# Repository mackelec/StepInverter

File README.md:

# StepInverter
These are the Files and Tools for my Step Inverter based on Tony's (WarpSpeed) designs and ideas.
You'll find me, "MackOffGrid" and Tony, "WarpSpeed" on https://www.thebackshed.com/forum/forum_topics.asp?FID=4 

Please keep in mind that the spreadsheet, software and schematics are not polished for public consumption, I created them for myself to get the job done.

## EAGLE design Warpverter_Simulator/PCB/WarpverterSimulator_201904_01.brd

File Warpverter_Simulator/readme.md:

# Warpverter Simulator

The simulator reads the signals from a Warpverter of any kind, and produces an analog output that you can view using a Scope.  It can also capture a frame of data and send the data to a PC.

## Instruction

This PCB plugs into the 38 pin header of tha Aduno DUE.

Then plug the outputs of Tony's Inverter, or stm32_Warpverter, into the matching connectors of the simulator PCB.
Connect your oscilloscope to DAC0 of the DUE to see the synthesized waveform.

Press the button on the simulator PCB and it will grab a frame of data and send it (by USB) to your PC.  Using the Arduino IDE serial monitor is the easiest way.

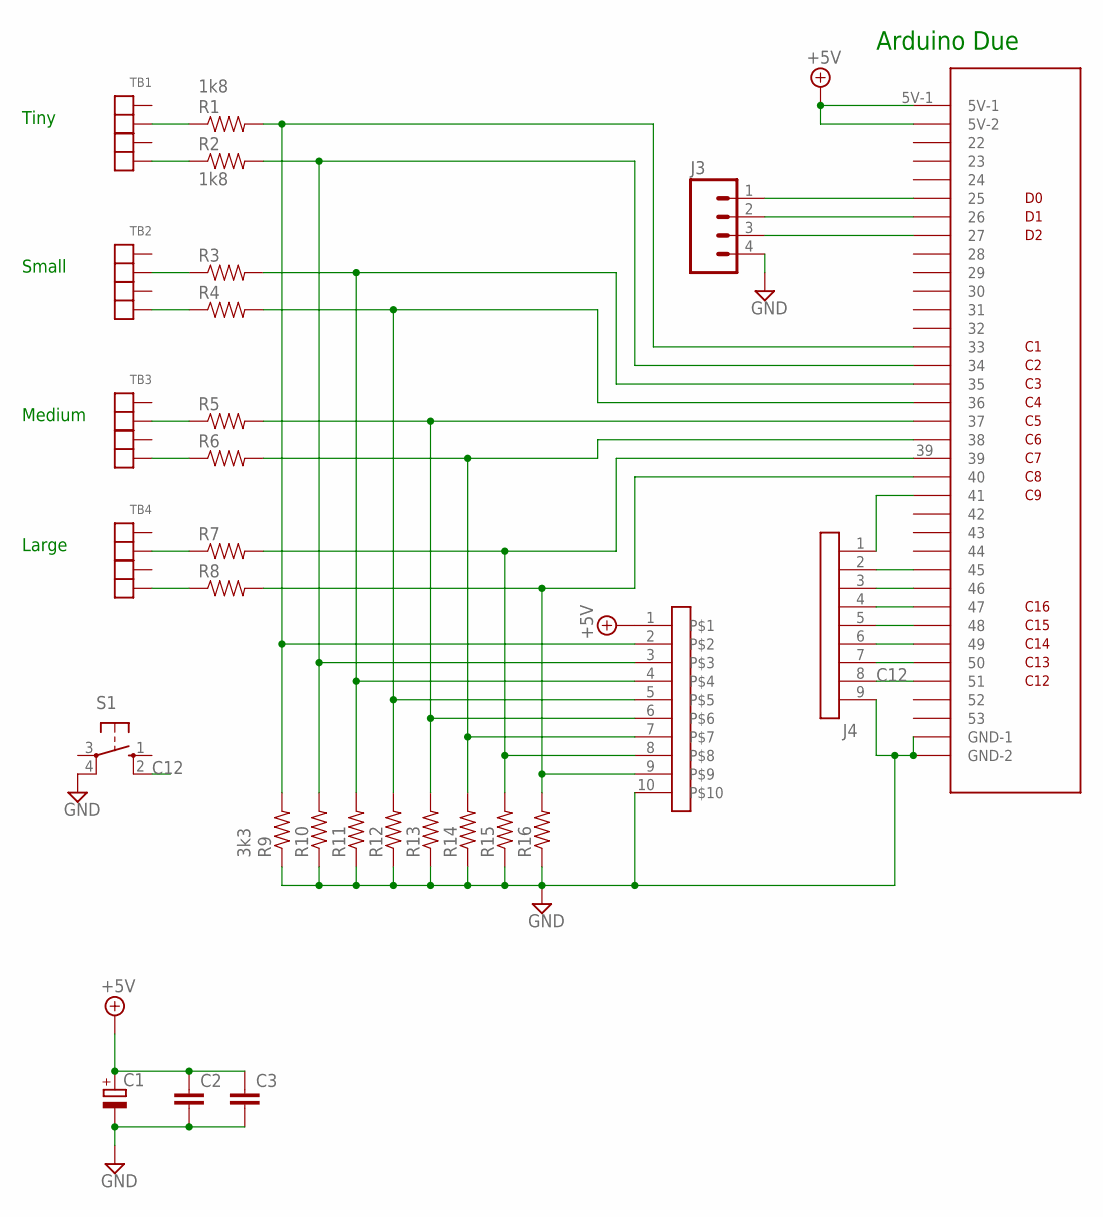
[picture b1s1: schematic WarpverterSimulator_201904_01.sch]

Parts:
C1: C-RB200100; CPOL-RADIAL-10UF-25V
C2, C3: BCAP
J1: DUE-IDC38
J2: SIL-STACK-10
J3: SIL4
J4: SIL-9
R1, R2: 1k8; AXIAL-0.4
R3, R4, R5, R6, R7, R8, R10, R11, R12, R13, R14, R15, R16: R4; AXIAL-0.4
R9: 3k3; AXIAL-0.4
S1: 10-XX; B3F-10XX
TB1, TB2, TB3, TB4: TB4381_SIL; TB-381-SIL-4P

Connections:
+5V: C1.1 (+), C2.1, C3.1, J1.5V-1, J1.5V-2, J2.1
C12: J1.51, J4.8, S1.2 (S1)
GND: C1.2 (-), C2.2, C3.2, J1.GND-1, J1.GND-2, J2.10, J3.4, J4.9, R9.P$1 (1), R10.P$1 (1), R11.P$1 (1), R12.P$1 (1), R13.P$1 (1), R14.P$1 (1), R15.P$1 (1), R16.P$1 (1), S1.4 (P1)
unnamed: R1.P$1 (1), TB1.2, TB1.12 (2)
unnamed: R2.P$1 (1), TB1.4, TB1.14 (4)
unnamed: R3.P$1 (1), TB2.2, TB2.12 (2)
unnamed: R4.P$1 (1), TB2.4, TB2.14 (4)
unnamed: R5.P$1 (1), TB3.2, TB3.12 (2)
unnamed: R6.P$1 (1), TB3.4, TB3.14 (4)
unnamed: R7.P$1 (1), TB4.2, TB4.12 (2)
unnamed: R8.P$1 (1), TB4.4, TB4.14 (4)
unnamed: J1.33, J2.2, R1.P$2 (2), R9.P$2 (2)
unnamed: J1.34, J2.3, R2.P$2 (2), R10.P$2 (2)
unnamed: J1.35, J2.4, R3.P$2 (2), R11.P$2 (2)
unnamed: J1.36, J2.5, R4.P$2 (2), R12.P$2 (2)
unnamed: J1.37, J2.6, R5.P$2 (2), R13.P$2 (2)
unnamed: J1.38, J2.7, R6.P$2 (2), R14.P$2 (2)
unnamed: J1.39, J2.8, R7.P$2 (2), R15.P$2 (2)
unnamed: J1.40, J2.9, R8.P$2 (2), R16.P$2 (2)
unnamed: J1.25, J3.1
unnamed: J1.26, J3.2
unnamed: J1.27, J3.3
unnamed: J1.50, J4.7
unnamed: J1.49, J4.6
unnamed: J1.48, J4.5
unnamed: J1.47, J4.4
unnamed: J1.46, J4.3
unnamed: J1.45, J4.2
unnamed: J1.41, J4.1

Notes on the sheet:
Tiny
Small
Medium
Large
Arduino Due

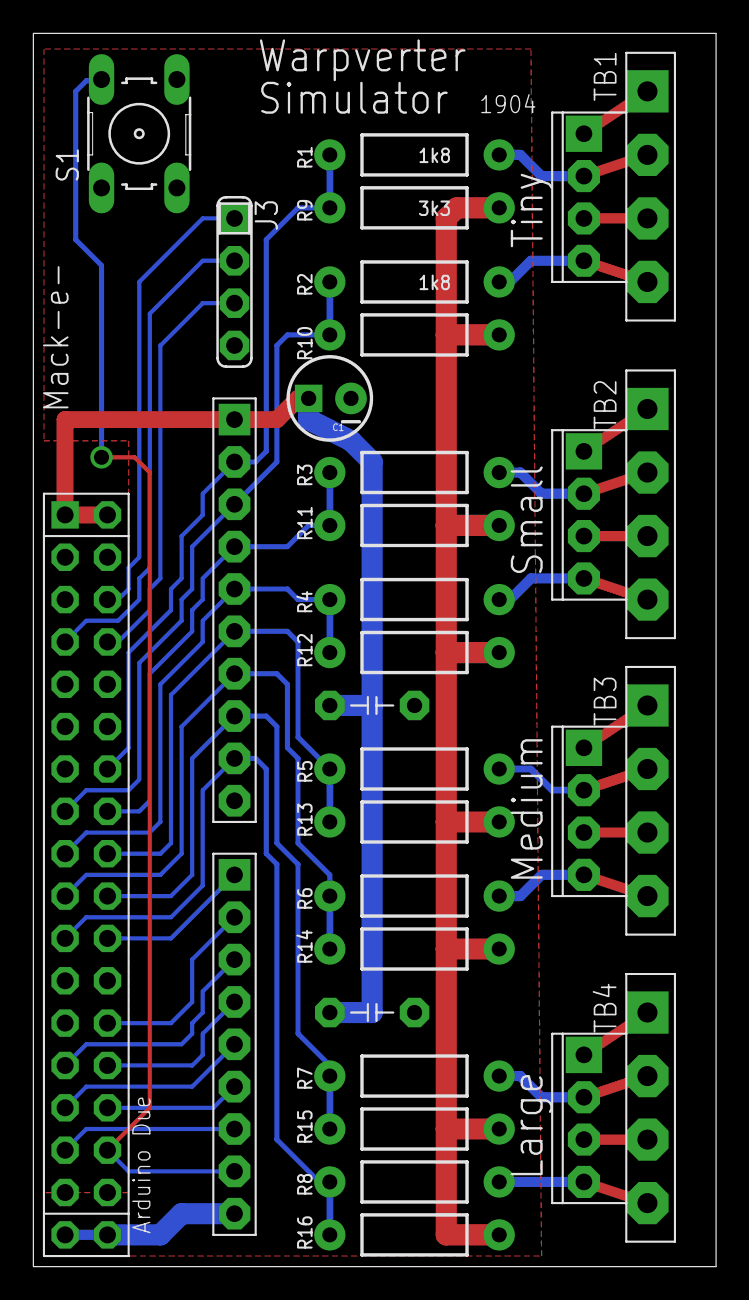
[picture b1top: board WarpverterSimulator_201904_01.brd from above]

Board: 2 copper layers, 40.9 x 74.0 mm, 28 parts (0 on the bottom side), 29 nets.

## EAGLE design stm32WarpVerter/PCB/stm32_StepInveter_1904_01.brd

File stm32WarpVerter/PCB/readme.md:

Zip Files contain EAGLE files and Gerber files.

For gerber viewer,  http://gerbv.geda-project.org/

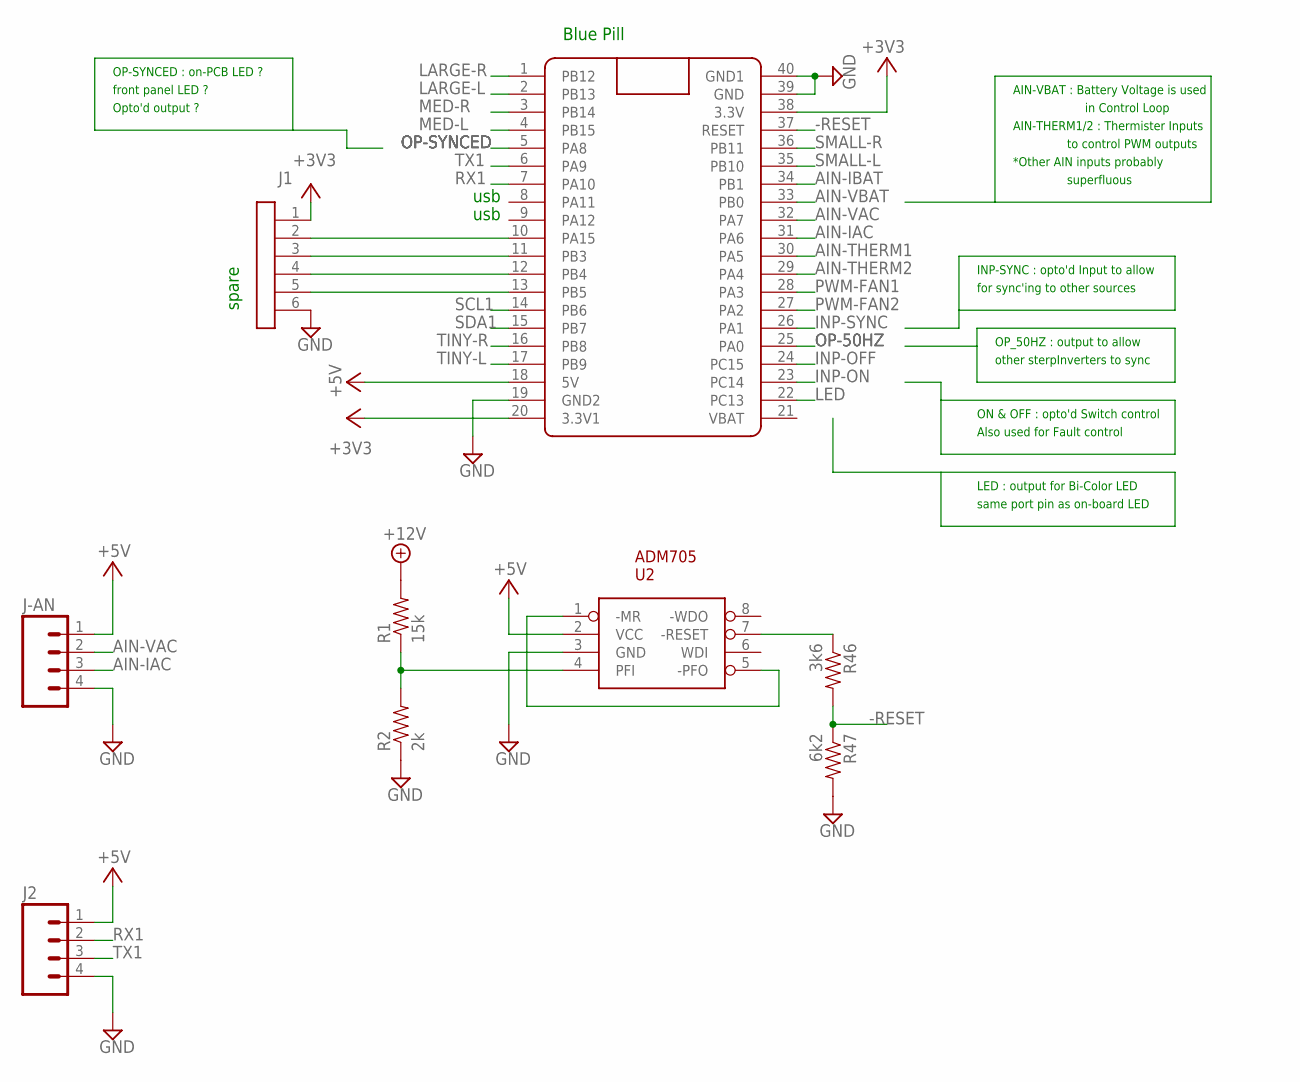
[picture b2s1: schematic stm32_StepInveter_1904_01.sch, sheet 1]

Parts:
J1: SIL-6; SIL6
J2: SIL4
J-AN: SIL4
R1: 15k; AXIAL-0.4
R2: 2k; AXIAL-0.4
R46: 3k6; AXIAL-0.4
R47: 6k2; AXIAL-0.4
U2: ADM705; DIL08
U$1: BLUE_PILL; BLUE_PILL_CLEAN

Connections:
+3V3: J1.1, U$1.20 (3.3V1), U$1.38 (3.3V); also elsewhere on the board
+5V: J2.1, J-AN.1, U2.2 (VCC), U$1.18 (5V); also elsewhere on the board
+12V: R1.P$2 (2); also elsewhere on the board
-RESET: R46.P$2 (2), R47.P$1 (1), U$1.37 (RESET)
AIN-IAC: J-AN.3, U$1.31 (PA6)
AIN-IBAT: U$1.34 (PB1); also elsewhere on the board
AIN-THERM1: U$1.30 (PA5); also elsewhere on the board
AIN-THERM2: U$1.29 (PA4); also elsewhere on the board
AIN-VAC: J-AN.2, U$1.32 (PA7)
AIN-VBAT: U$1.33 (PB0); also elsewhere on the board
GND: J1.6, J2.4, J-AN.4, R2.P$1 (1), R47.P$2 (2), U2.3 (GND), U$1.19 (GND2), U$1.39 (GND), U$1.40 (GND1); also elsewhere on the board
INP-OFF: U$1.24 (PC15); also elsewhere on the board
INP-ON: U$1.23 (PC14); also elsewhere on the board
INP-SYNC: U$1.26 (PA1); also elsewhere on the board
LARGE-L: U$1.2 (PB13); also elsewhere on the board
LARGE-R: U$1.1 (PB12); also elsewhere on the board
LED: U$1.22 (PC13); also elsewhere on the board
MED-L: U$1.4 (PB15); also elsewhere on the board
MED-R: U$1.3 (PB14); also elsewhere on the board
unnamed: J1.2, U$1.10 (PA15)
unnamed: J1.3, U$1.11 (PB3)
unnamed: J1.4, U$1.12 (PB4)
unnamed: J1.5, U$1.13 (PB5)
unnamed: U2.1 (-MR), U2.5 (-PFO)
unnamed: R1.P$1 (1), R2.P$2 (2), U2.4 (PFI)
unnamed: R46.P$1 (1), U2.7 (-RESET)
OP-50HZ: U$1.25 (PA0); also elsewhere on the board
OP-SYNCED: U$1.5 (PA8); also elsewhere on the board
PWM-FAN1: U$1.28 (PA3); also elsewhere on the board
PWM-FAN2: U$1.27 (PA2); also elsewhere on the board
RX1: J2.2, U$1.7 (PA10)
SCL1: U$1.14 (PB6)
SDA1: U$1.15 (PB7)
SMALL-L: U$1.35 (PB10); also elsewhere on the board
SMALL-R: U$1.36 (PB11); also elsewhere on the board
TINY-L: U$1.17 (PB9); also elsewhere on the board
TINY-R: U$1.16 (PB8); also elsewhere on the board
TX1: J2.3, U$1.6 (PA9)

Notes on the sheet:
usb
spare
Blue Pill
OP_50HZ : output to allow
other sterpInverters to sync
ON & OFF : opto'd Switch control
Also used for Fault control
LED : output for Bi-Color LED
same port pin as on-board LED
INP-SYNC : opto'd Input to allow
for sync'ing to other sources
OP-SYNCED : on-PCB LED ?
front panel LED ?
Opto'd output ?
AIN-VBAT : Battery Voltage is used
in Control Loop
AIN-THERM1/2 : Thermister Inputs
to control PWM outputs
*Other AIN inputs probably
superfluous

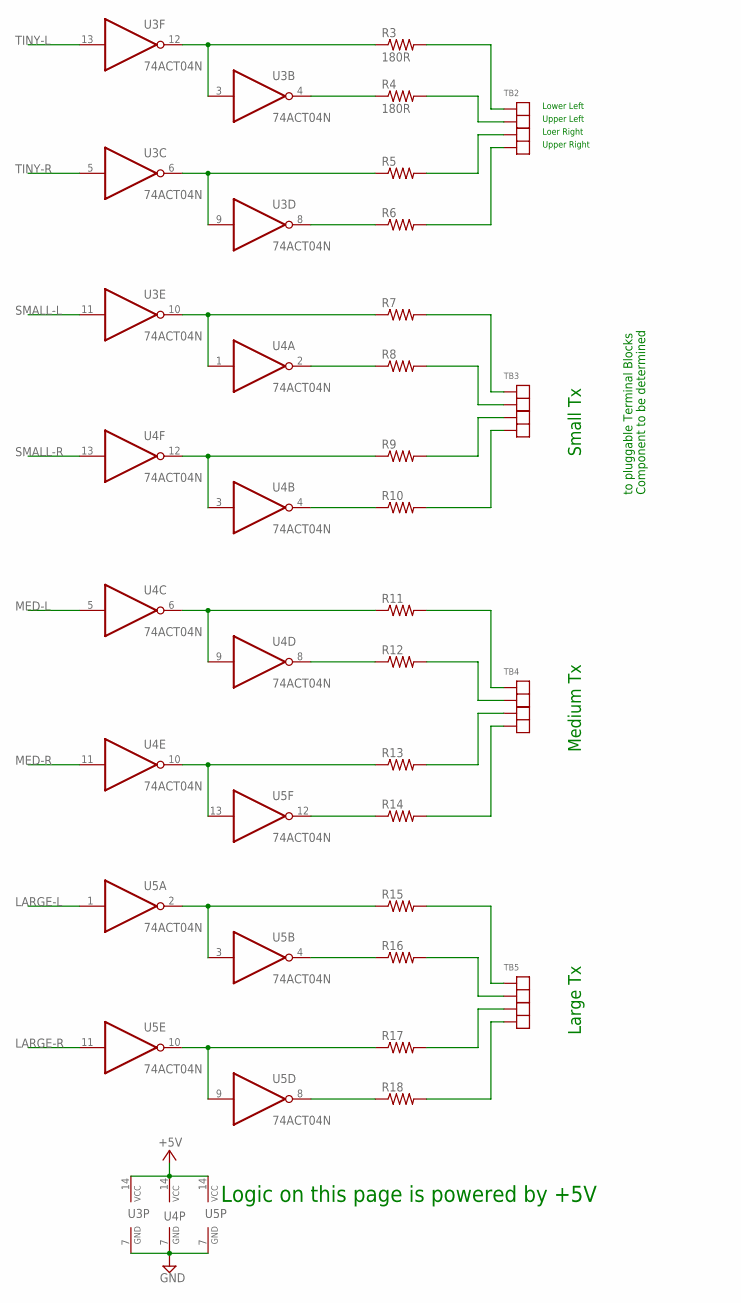
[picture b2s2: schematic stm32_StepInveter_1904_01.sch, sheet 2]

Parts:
R3, R4: 180R; AXIAL-0.4
R5, R6, R7, R8, R9, R10, R11, R12, R13, R14, R15, R16, R17, R18: R4; AXIAL-0.4
TB2, TB3, TB4, TB5: TB4381_SIL; TB-381-SIL-4P
U3, U4, U5: 74ACT04N; DIL14

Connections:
+5V: U3.14 (VCC), U4.14 (VCC), U5.14 (VCC); also elsewhere on the board
GND: U3.7 (GND), U4.7 (GND), U5.7 (GND); also elsewhere on the board
LARGE-L: U5.1 (I); also elsewhere on the board
LARGE-R: U5.11 (I); also elsewhere on the board
MED-L: U4.5 (I); also elsewhere on the board
MED-R: U4.11 (I); also elsewhere on the board
unnamed: R3.P$1 (1), U3.3 (I), U3.12 (O)
unnamed: R4.P$1 (1), U3.4 (O)
unnamed: R5.P$1 (1), U3.6 (O), U3.9 (I)
unnamed: R6.P$1 (1), U3.8 (O)
unnamed: R7.P$1 (1), U3.10 (O), U4.1 (I)
unnamed: R8.P$1 (1), U4.2 (O)
unnamed: R9.P$1 (1), U4.3 (I), U4.12 (O)
unnamed: R10.P$1 (1), U4.4 (O)
unnamed: R11.P$1 (1), U4.6 (O), U4.9 (I)
unnamed: R12.P$1 (1), U4.8 (O)
unnamed: R13.P$1 (1), U4.10 (O), U5.13 (I)
unnamed: R14.P$1 (1), U5.12 (O)
unnamed: R15.P$1 (1), U5.2 (O), U5.3 (I)
unnamed: R16.P$1 (1), U5.4 (O)
unnamed: R17.P$1 (1), U5.9 (I), U5.10 (O)
unnamed: R18.P$1 (1), U5.8 (O)
unnamed: R3.P$2 (2), TB2.1, TB2.11 (1)
unnamed: R4.P$2 (2), TB2.2, TB2.12 (2)
unnamed: R5.P$2 (2), TB2.3, TB2.13 (3)
unnamed: R6.P$2 (2), TB2.4, TB2.14 (4)
unnamed: R7.P$2 (2), TB3.1, TB3.11 (1)
unnamed: R8.P$2 (2), TB3.2, TB3.12 (2)
unnamed: R9.P$2 (2), TB3.3, TB3.13 (3)
unnamed: R10.P$2 (2), TB3.4, TB3.14 (4)
unnamed: R11.P$2 (2), TB4.1, TB4.11 (1)
unnamed: R12.P$2 (2), TB4.2, TB4.12 (2)
unnamed: R13.P$2 (2), TB4.3, TB4.13 (3)
unnamed: R14.P$2 (2), TB4.4, TB4.14 (4)
unnamed: R15.P$2 (2), TB5.1, TB5.11 (1)
unnamed: R16.P$2 (2), TB5.2, TB5.12 (2)
unnamed: R17.P$2 (2), TB5.3, TB5.13 (3)
unnamed: R18.P$2 (2), TB5.4, TB5.14 (4)
SMALL-L: U3.11 (I); also elsewhere on the board
SMALL-R: U4.13 (I); also elsewhere on the board
TINY-L: U3.13 (I); also elsewhere on the board
TINY-R: U3.5 (I); also elsewhere on the board

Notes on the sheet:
Logic on this page is powered by +5V
to pluggable Terminal Blocks
Component to be determined
Lower Left
Upper Left
Loer Right
Upper Right
Large Tx
Medium Tx
Small Tx

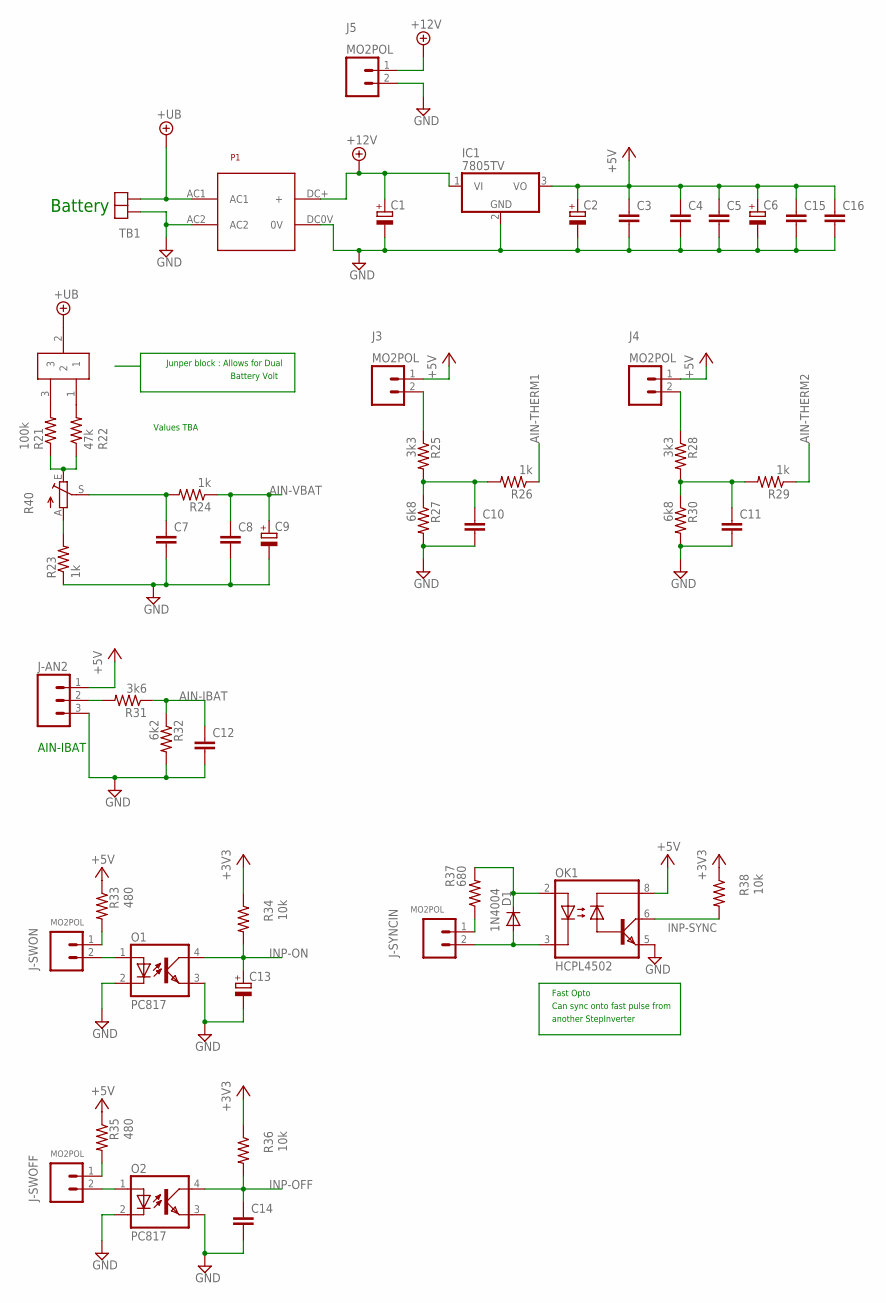
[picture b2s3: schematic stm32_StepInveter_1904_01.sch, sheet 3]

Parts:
C1: CPOL-EUE5-8.5; E5-8,5
C2, C6, C9: CPOL-EUE2.5-5; E2,5-5
C3, C4, C5, C7, C8, C10, C11, C12, C14, C15, C16: BCAP
C13: CPOL-EUE2.5-6; E2,5-6
D1: 1N4004; DO41-10
IC1: 7805TV; TO220V
J3, J4, J5: MO2POL; MOLEX-1X2
J-AN2: MO3POL; MOLEX-3
J-SWOFF: MO2POL; MOLEX-1X2
J-SWON: MO2POL; MOLEX-1X2
J-SYNCIN: MO2POL; MOLEX-1X2
JP1: JP1X3
O1, O2: PC817; DIL04
OK1: HCPL4502; DIL08
P1: ACDC
R21: 100k; AXIAL-0.4
R22: 47k; AXIAL-0.4
R23, R24, R26, R29: 1k; AXIAL-0.4
R25, R28: 3k3; AXIAL-0.4
R27, R30: 6k8; AXIAL-0.4
R31: 3k6; AXIAL-0.4
R32: 6k2; AXIAL-0.4
R33, R35: 480; AXIAL-0.4
R34, R36, R38: 10k; AXIAL-0.4
R37: 680; AXIAL-0.4
R40: TRIM_EU-B64Y; B64Y
TB1: TB2381; TB-KF2EDG381-2P

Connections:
+3V3: R34.P$1 (1), R36.P$1 (1), R38.P$1 (1); also elsewhere on the board
+5V: C2.+, C3.1, C4.1, C5.1, C6.+, C15.1, C16.1, IC1.3 (VO), J3.1, J4.1, J-AN2.1, OK1.8 (VCC), R33.P$1 (1), R35.P$1 (1); also elsewhere on the board
+12V: C1.+, IC1.1 (VI), J5.1, P1.DC+ (+); also elsewhere on the board
+UB: JP1.2, P1.AC1, TB1.1
AIN-IBAT: C12.1, R31.P$1 (1), R32.P$1 (1); also elsewhere on the board
AIN-THERM1: R26.P$1 (1); also elsewhere on the board
AIN-THERM2: R29.P$1 (1); also elsewhere on the board
AIN-VBAT: C8.1, C9.+, R24.P$1 (1); also elsewhere on the board
GND: C1.-, C2.-, C3.2, C4.2, C5.2, C6.-, C7.2, C8.2, C9.-, C10.2, C11.2, C12.2, C13.-, C14.2, C15.2, C16.2, IC1.2 (GND), J5.2, J-AN2.3, O1.2 (C), O1.3 (EMIT), O2.2 (C), O2.3 (EMIT), OK1.5 (GND), P1.AC2, P1.DC0V (0V), R23.P$1 (1), R27.P$2 (2), R30.P$2 (2), R32.P$2 (2), TB1.2; also elsewhere on the board
INP-OFF: C14.1, O2.4 (COL), R36.P$2 (2); also elsewhere on the board
INP-ON: C13.+, O1.4 (COL), R34.P$2 (2); also elsewhere on the board
INP-SYNC: OK1.6 (VO), R38.P$2 (2); also elsewhere on the board
unnamed: JP1.3, R21.P$2 (2)
unnamed: JP1.1, R22.P$2 (2)
unnamed: R21.P$1 (1), R22.P$1 (1), R40.E
unnamed: C10.1, R25.P$2 (2), R26.P$2 (2), R27.P$1 (1)
unnamed: J4.2, R28.P$1 (1)
unnamed: J3.2, R25.P$1 (1)
unnamed: C11.1, R28.P$2 (2), R29.P$2 (2), R30.P$1 (1)
unnamed: J-SWON.1, R33.P$2 (2)
unnamed: J-AN2.2, R31.P$2 (2)
unnamed: J-SWON.2, O1.1 (A)
unnamed: J-SYNCIN.1, R37.P$1 (1)
unnamed: D1.A, J-SYNCIN.2, OK1.3 (C)
unnamed: J-SWOFF.1, R35.P$2 (2)
unnamed: J-SWOFF.2, O2.1 (A)
unnamed: D1.C, OK1.2 (A), R37.P$2 (2)
unnamed: C7.1, R24.P$2 (2), R40.S
unnamed: R23.P$2 (2), R40.A

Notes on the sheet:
Battery
Values TBA
Junper block : Allows for Dual
Battery Volt
AIN-IBAT
Fast Opto
Can sync onto fast pulse from
another StepInverter

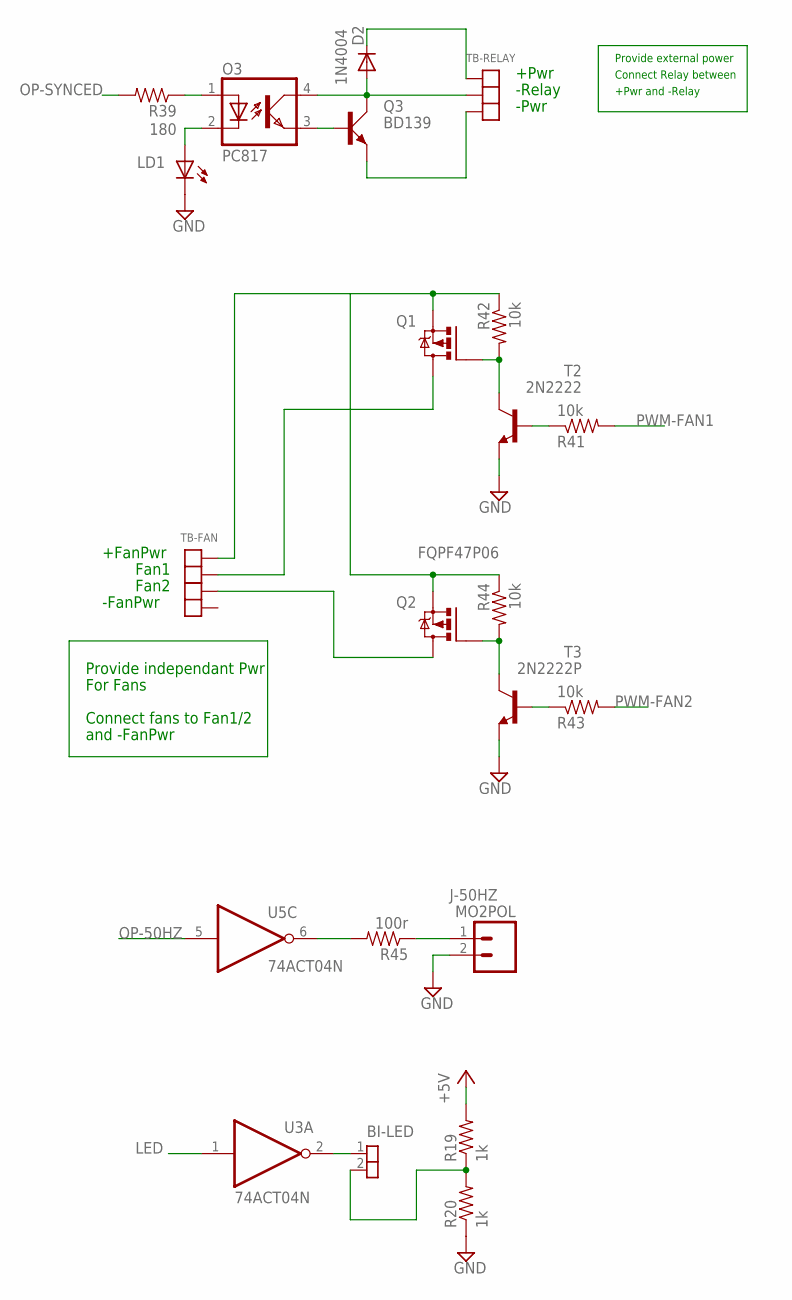
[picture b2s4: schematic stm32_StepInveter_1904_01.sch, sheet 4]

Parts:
BI-LED: SIL-2; JP1
D2: 1N4004; DO41-10
J-50HZ: MO2POL; MOLEX-1X2
LD1: LED3MM
O3: PC817; DIL04
Q1: MOSFET-PCHFQPF47P06; TO220BV
Q2: FQPF47P06; TO220BV
Q3: BD139; TO126AV
R19, R20: 1k; AXIAL-0.4
R39: 180; AXIAL-0.4
R41, R42, R43, R44: 10k; AXIAL-0.4
R45: 100r; AXIAL-0.4
T2: 2N2222; TO92/
T3: 2N2222P; TO92/
TB-FAN: TB4; TB-KF2EDG381-4P
TB-RELAY: TB3381; TB-KF2EDG381-3P
U3, U5: 74ACT04N; DIL14

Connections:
+5V: R19.P$2 (2); also elsewhere on the board
GND: J-50HZ.2, LD1.K (C), R20.P$1 (1), T2.1 (E), T3.1 (E); also elsewhere on the board
LED: U3.1 (I); also elsewhere on the board
unnamed: BI-LED.2, R19.P$1 (1), R20.P$2 (2)
unnamed: BI-LED.1, U3.2 (O)
unnamed: LD1.A, O3.2 (C)
unnamed: O3.1 (A), R39.P$1 (1)
unnamed: Q1.G, R42.P$2 (2), T2.3 (C)
unnamed: O3.3 (EMIT), Q3.B
unnamed: R41.P$1 (1), T2.2 (B)
unnamed: Q1.S, Q2.S, R42.P$1 (1), R44.P$1 (1), TB-FAN.1
unnamed: Q2.G, R44.P$2 (2), T3.3 (C)
unnamed: R45.P$2 (2), U5.6 (O)
unnamed: Q1.D, TB-FAN.2
unnamed: R43.P$1 (1), T3.2 (B)
unnamed: J-50HZ.1, R45.P$1 (1)
unnamed: Q2.D, TB-FAN.3
unnamed: D2.A, O3.4 (COL), Q3.C, TB-RELAY.2
unnamed: D2.C, TB-RELAY.1
unnamed: Q3.E, TB-RELAY.3
OP-50HZ: U5.5 (I); also elsewhere on the board
OP-SYNCED: R39.P$2 (2); also elsewhere on the board
PWM-FAN1: R41.P$2 (2); also elsewhere on the board
PWM-FAN2: R43.P$2 (2); also elsewhere on the board

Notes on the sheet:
+FanPwr
-FanPwr
Fan1
Fan2
Provide independant Pwr
For Fans
Connect fans to Fan1/2
and -FanPwr
+Pwr
-Pwr
-Relay
Connect Relay between
+Pwr and -Relay
Provide external power

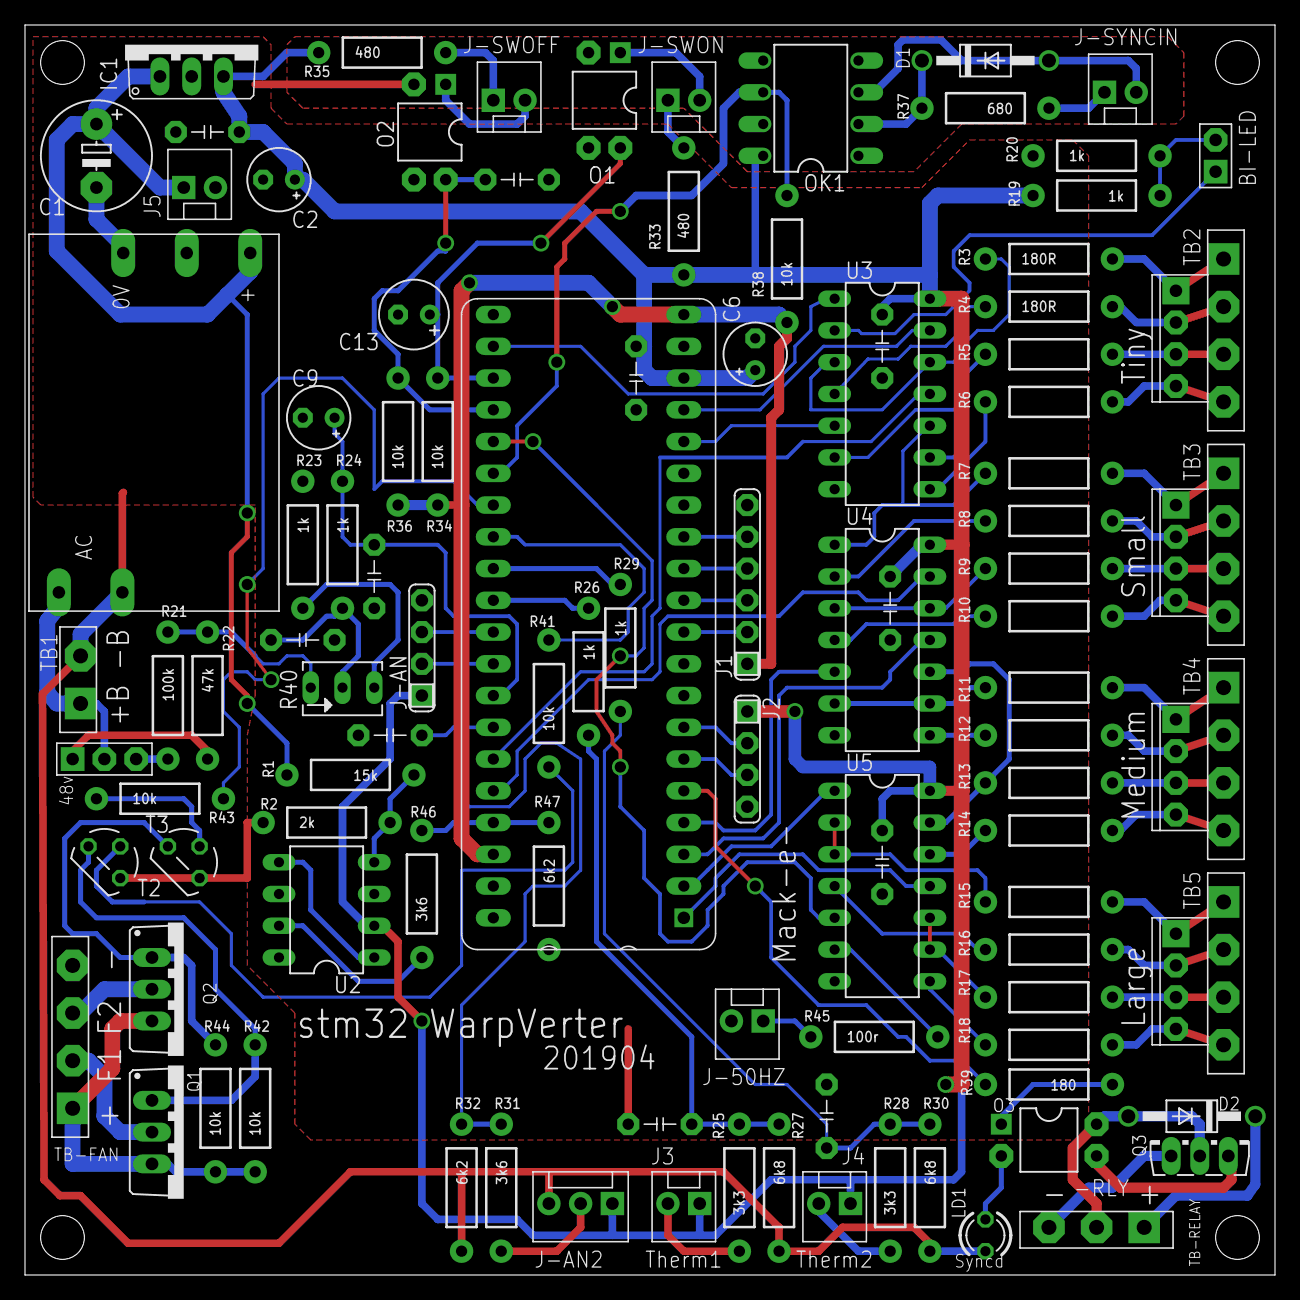
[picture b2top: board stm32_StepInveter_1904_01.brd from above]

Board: 2 copper layers, 100.0 x 100.0 mm, 102 parts (0 on the bottom side), 103 nets.

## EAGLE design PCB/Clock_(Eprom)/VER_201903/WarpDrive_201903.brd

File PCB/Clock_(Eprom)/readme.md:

## Warpverter Clock PCB

This PCB contructs is the heart of the Warpverter.  It uses an Eprom to construct the four inverter drive signals.

### VER 201903

This is my latest version. Fixed an oops on the previous version.  Major changes to the micro port, uses a crystal module instead of a discrete circuit, added a sync connector for my experiment on three phase.  Added a Bi-colour LED for Run/Stop.  Changed the PSU supervisor to max705.

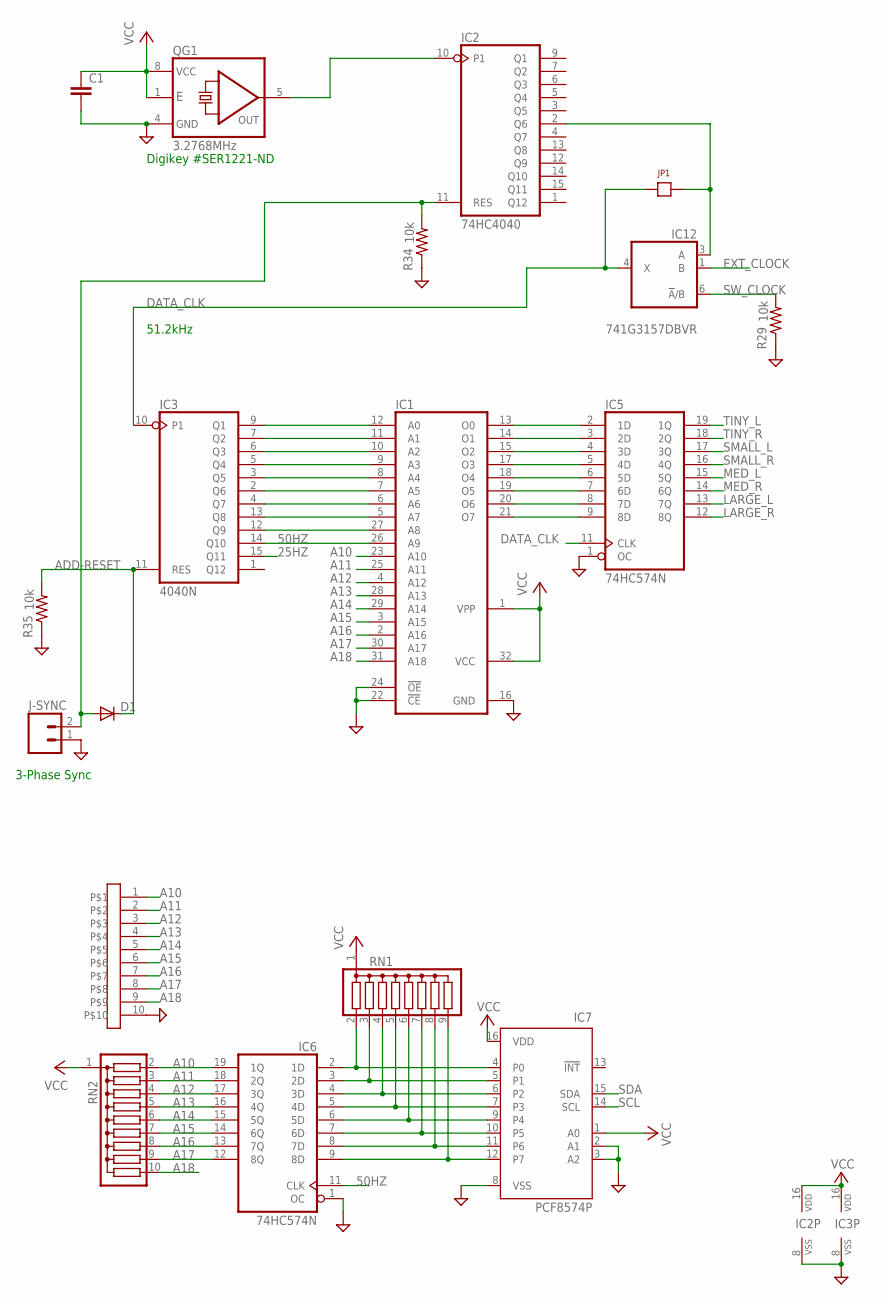
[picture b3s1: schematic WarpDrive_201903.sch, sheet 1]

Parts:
C1: BCAP
D1: 1N4148DO35-7; D3
IC1: 27C4001D; DIL32
IC2: 74HC4040; DIL16
IC3: 4040N; DIL16
IC5, IC6: 74HC574N; DIL20
IC7: PCF8574P; DIL16
IC12: 741G3157DBVR; DBV_R-PDSO-G6
J1: SIL-STACK-10
J-SYNC: MO2POL; MOLEX-1X2
JP1: JP1
QG1: 3.2768MHz; DIL08-4
R29, R34, R35: 10k; AXIAL-0.4
RN1: G08R; SIL9
RN2: G09R; SIL10

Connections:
25HZ: IC3.15 (Q11)
50HZ: IC1.26 (A9), IC3.14 (Q10), IC6.11 (CLK); also elsewhere on the board
A10: IC1.23 (A10), IC6.19 (1Q), J1.1, RN2.2
A11: IC1.25 (A11), IC6.18 (2Q), J1.2, RN2.3
A12: IC1.4 (A12), IC6.17 (3Q), J1.3, RN2.4
A13: IC1.28 (A13), IC6.16 (4Q), J1.4, RN2.5
A14: IC1.29 (A14), IC6.15 (5Q), J1.5, RN2.6
A15: IC1.3 (A15), IC6.14 (6Q), J1.6, RN2.7
A16: IC1.2 (A16), IC6.13 (7Q), J1.7, RN2.8
A17: IC1.30 (A17), IC6.12 (8Q), J1.8, RN2.9
A18: IC1.31 (A18), J1.9, RN2.10; also elsewhere on the board
ADD-RESET: D1.C, IC3.11 (RES), R35.P$2 (2); also elsewhere on the board
DATA_CLK: IC3.10 (P1), IC5.11 (CLK), IC12.4 (X), JP1.1; also elsewhere on the board
EXT_CLOCK: IC12.1 (B); also elsewhere on the board
GND: C1.2, IC1.16 (GND), IC1.22 (!CE), IC1.24 (!OE), IC2.8 (VSS), IC3.8 (VSS), IC5.1 (OC), IC5.10 (GND), IC6.1 (OC), IC6.10 (GND), IC7.2 (A1), IC7.3 (A2), IC7.8 (VSS), IC12.2 (GND), J1.10, J-SYNC.1, QG1.4 (GND), R29.P$1 (1), R34.P$1 (1), R35.P$1 (1); also elsewhere on the board
LARGE_L: IC5.13 (7Q); also elsewhere on the board
LARGE_R: IC5.12 (8Q); also elsewhere on the board
MED_L: IC5.15 (5Q); also elsewhere on the board
MED_R: IC5.14 (6Q); also elsewhere on the board
unnamed: IC2.10 (P1), QG1.5 (OUT)
unnamed: IC1.12 (A0), IC3.9 (Q1)
unnamed: IC1.11 (A1), IC3.7 (Q2)
unnamed: IC1.10 (A2), IC3.6 (Q3)
unnamed: IC1.9 (A3), IC3.5 (Q4)
unnamed: IC1.8 (A4), IC3.3 (Q5)
unnamed: IC1.7 (A5), IC3.2 (Q6)
unnamed: IC1.6 (A6), IC3.4 (Q7)
unnamed: IC1.5 (A7), IC3.13 (Q8)
unnamed: IC1.27 (A8), IC3.12 (Q9)
unnamed: IC1.13 (O0), IC5.2 (1D)
unnamed: IC2.2 (Q6), IC12.3 (A), JP1.2
unnamed: IC1.14 (O1), IC5.3 (2D)
unnamed: IC6.2 (1D), IC7.4 (P0), RN1.2
unnamed: IC1.15 (O2), IC5.4 (3D)
unnamed: IC1.17 (O3), IC5.5 (4D)
unnamed: IC1.18 (O4), IC5.6 (5D)
unnamed: IC1.19 (O5), IC5.7 (6D)
unnamed: IC1.20 (O6), IC5.8 (7D)
unnamed: IC1.21 (O7), IC5.9 (8D)
unnamed: IC6.3 (2D), IC7.5 (P1), RN1.3
unnamed: IC6.4 (3D), IC7.6 (P2), RN1.4
unnamed: IC6.5 (4D), IC7.7 (P3), RN1.5
unnamed: IC6.6 (5D), IC7.9 (P4), RN1.6
unnamed: IC6.7 (6D), IC7.10 (P5), RN1.7
unnamed: IC6.8 (7D), IC7.11 (P6), RN1.8
unnamed: IC6.9 (8D), IC7.12 (P7), RN1.9
unnamed: D1.A, IC2.11 (RES), J-SYNC.2, R34.P$2 (2)
SCL: IC7.14 (SCL); also elsewhere on the board
SDA: IC7.15 (SDA); also elsewhere on the board
SMALL_L: IC5.17 (3Q); also elsewhere on the board
SMALL_R: IC5.16 (4Q); also elsewhere on the board
SW_CLOCK: IC12.6 (!A!/B), R29.P$2 (2); also elsewhere on the board
TINY_L: IC5.19 (1Q); also elsewhere on the board
TINY_R: IC5.18 (2Q); also elsewhere on the board
VCC: C1.1, IC1.1 (VPP), IC1.32 (VCC), IC2.16 (VDD), IC3.16 (VDD), IC5.20 (VCC), IC6.20 (VCC), IC7.1 (A0), IC7.16 (VDD), IC12.5 (VCC), QG1.1 (E), QG1.8 (VCC), RN1.1, RN2.1; also elsewhere on the board

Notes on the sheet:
51.2kHz
3-Phase Sync
Digikey #SER1221-ND

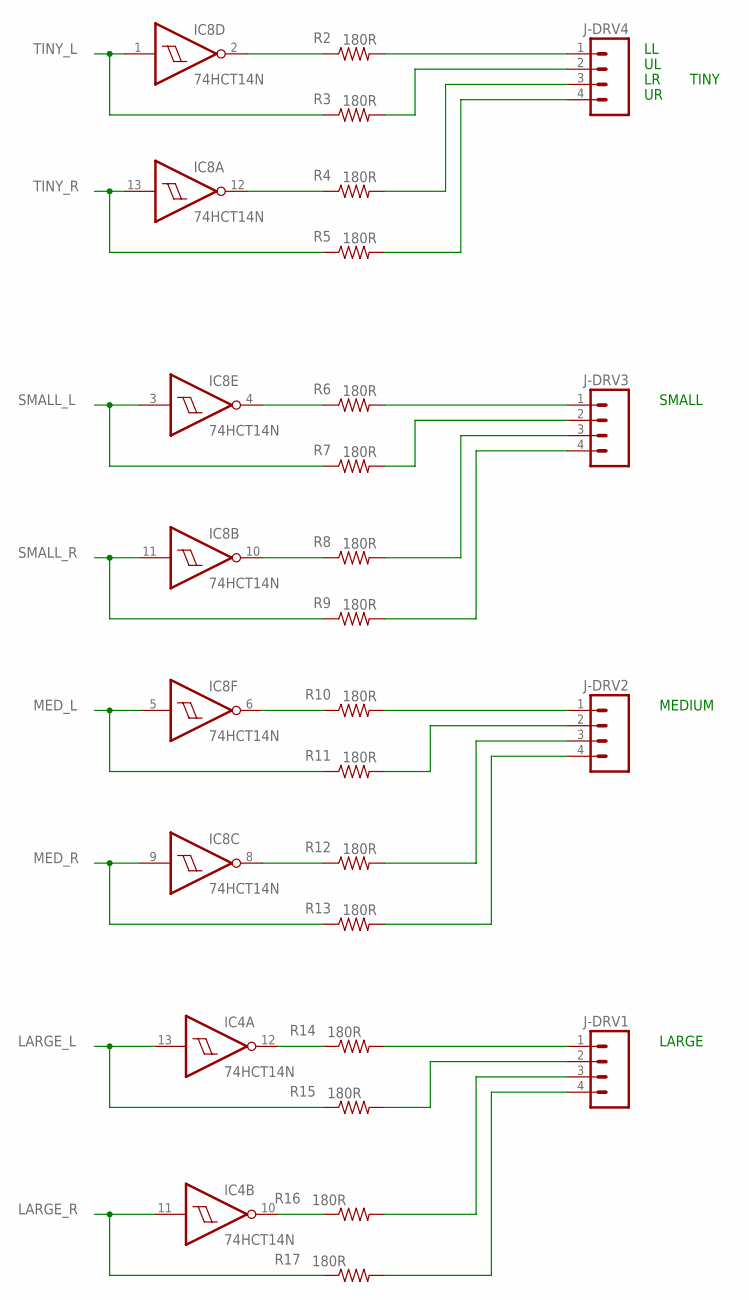
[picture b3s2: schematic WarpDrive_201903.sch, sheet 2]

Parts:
IC4, IC8: 74HCT14N; DIL14
J-DRV1, J-DRV2, J-DRV3, J-DRV4: MO4POL; MOLEX-4
R2, R3, R4, R5, R6, R7, R8, R9, R10, R11, R12, R13, R14, R15, R16, R17: 180R; AXIAL-0.4

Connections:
GND: IC4.7 (GND), IC8.7 (GND); also elsewhere on the board
LARGE_L: IC4.13 (I), R15.P$1 (1); also elsewhere on the board
LARGE_R: IC4.11 (I), R17.P$1 (1); also elsewhere on the board
MED_L: IC8.5 (I), R11.P$1 (1); also elsewhere on the board
MED_R: IC8.9 (I), R13.P$1 (1); also elsewhere on the board
unnamed: IC4.12 (O), R14.P$1 (1)
unnamed: IC4.10 (O), R16.P$1 (1)
unnamed: IC8.2 (O), R2.P$1 (1)
unnamed: J-DRV4.1, R2.P$2 (2)
unnamed: J-DRV4.2, R3.P$2 (2)
unnamed: IC8.12 (O), R4.P$1 (1)
unnamed: J-DRV4.3, R4.P$2 (2)
unnamed: J-DRV4.4, R5.P$2 (2)
unnamed: IC8.4 (O), R6.P$1 (1)
unnamed: J-DRV3.1, R6.P$2 (2)
unnamed: J-DRV3.2, R7.P$2 (2)
unnamed: IC8.10 (O), R8.P$1 (1)
unnamed: J-DRV3.3, R8.P$2 (2)
unnamed: J-DRV3.4, R9.P$2 (2)
unnamed: IC8.6 (O), R10.P$1 (1)
unnamed: J-DRV2.1, R10.P$2 (2)
unnamed: J-DRV2.2, R11.P$2 (2)
unnamed: IC8.8 (O), R12.P$1 (1)
unnamed: J-DRV2.3, R12.P$2 (2)
unnamed: J-DRV2.4, R13.P$2 (2)
unnamed: J-DRV1.1, R14.P$2 (2)
unnamed: J-DRV1.2, R15.P$2 (2)
unnamed: J-DRV1.3, R16.P$2 (2)
unnamed: J-DRV1.4, R17.P$2 (2)
SMALL_L: IC8.3 (I), R7.P$1 (1); also elsewhere on the board
SMALL_R: IC8.11 (I), R9.P$1 (1); also elsewhere on the board
TINY_L: IC8.1 (I), R3.P$1 (1); also elsewhere on the board
TINY_R: IC8.13 (I), R5.P$1 (1); also elsewhere on the board
VCC: IC4.14 (VCC), IC8.14 (VCC); also elsewhere on the board

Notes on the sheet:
TINY
SMALL
MEDIUM
LARGE

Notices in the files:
parts and their libraries:
SparkFun-Passives: Licensing: CC v3.0 Share-Alike You are welcome to use this library for commercial purposes.
